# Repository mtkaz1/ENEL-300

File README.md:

## Overview

This project is a **Bluetooth-controlled remote robot** built by a 4-member team to compete in an obstacle course and metal/object detection challenge, where we placed **Top 10**. The robot combines custom PCB design, embedded firmware, and real-time sensor integration to navigate obstacles and detect objects autonomously and via manual override.

## Key Features

- **Bluetooth Control**: Real-time remote driving via a Bluetooth serial link, allowing manual navigation through the obstacle course alongside autonomous detection routines.
- **ESP32 Firmware (C)**: Core embedded logic written in **C**, handling motor control via **PWM**, sensor polling, and Bluetooth command parsing simultaneously.
- **Remote Control App (Python)**: Built a **Python** application to send driving commands over Bluetooth, giving the operator real-time manual control during competition runs.
- **Custom PCB Design**: Designed and fabricated a custom PCB to consolidate power distribution, motor drivers, and sensor connections, reducing wiring complexity and improving reliability during competition runs.
- **Object/Metal Detection**: Integrated sensors for object and metal detection, feeding data back to the ESP32 for navigation decisions.
- **PWM Motor Control**: Used **PWM** signals to precisely control motor speed and direction, enabling fine-tuned maneuvering through tight obstacle course sections.

## Development Process

Our team of 4 applied a sprint-based workflow, using Gantt charts and weekly check-ins to track progress and keep hardware and firmware development in sync. This let us parallelize PCB fabrication, firmware development, and mechanical assembly, then integrate and test the full system ahead of competition.

## Results

The robot placed **Top 10** in the obstacle course and object detection competition, validating both the reliability of our custom PCB/hardware stack and the responsiveness of our Bluetooth control and detection firmware under competition conditions.

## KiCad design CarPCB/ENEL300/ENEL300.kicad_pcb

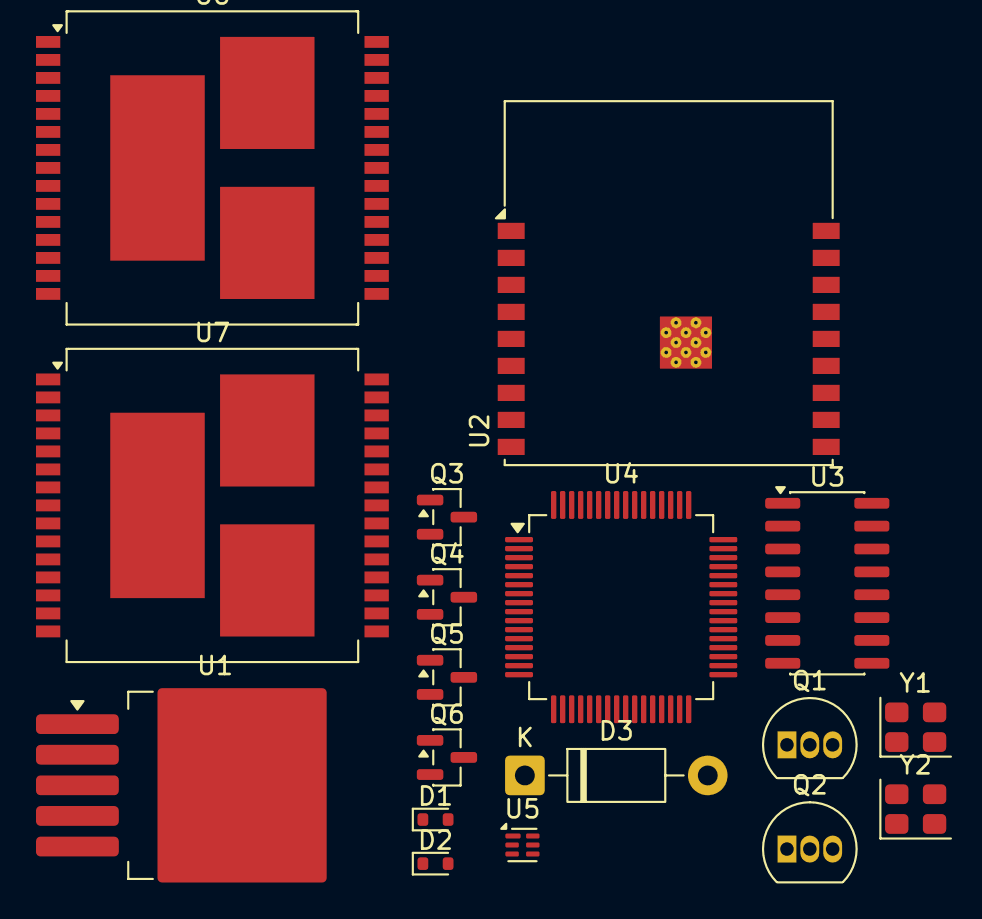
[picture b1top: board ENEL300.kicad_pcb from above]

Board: 2 copper layers, 18 parts (0 on the bottom side), 25 nets, no tracks yet.

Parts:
D1, D2: ESD5Zxx; D_SOD-523
D3: 1N5824; D_DO-41_SOD81_P10.16mm_Horizontal
Q1, Q2: 2N3904; TO-92_Inline
Q3, Q4, Q5, Q6: 2N7002E; SOT-23
U1: LM2596S-5; TO-263-5_TabPin3
U2: ESP32-C3-WROOM-02
U3: CH340C; SOIC-16_3.9x9.9mm_P1.27mm
U4: STM32F446RETx; LQFP-64_10x10mm_P0.5mm
U5: BQ297xy; WSON-6_1.5x1.5mm_P0.5mm
U6, U7: VNH5019A-E; ST_MultiPowerSO-30
Y1, Y2: ASE-xxxMHz; Oscillator_SMD_Abracon_ASE-4Pin_3.2x2.5mm

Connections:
+3.3V: U1.4 (FB), U2.1 (3V3), U3.16 (VCC), U4.1 (VBAT), U4.19 (VDD), U4.32 (VDD), U4.48 (VDD), U4.64 (VDD), Y1.4 (Vdd), Y2.4 (Vdd)
+BATT: Q5.2 (S), Q6.2 (S), U1.1 (VIN), U6.12 (VBAT), U7.12 (VBAT)
GND: D3.2 (A), Q1.1 (E), Q1.3 (C), Q2.1 (E), Q4.2 (S), U1.3 (GND), U1.5 (~ON/OFF), U2.8 (IO9), U2.9 (GND), U2.19 (GND), U3.1 (GND), U4.12 (VSSA), U4.18 (VSS), U4.31 (VSS), U4.47 (VSS), U4.63 (VSS), U6.18 (GNDB), U6.19 (GNDB), U6.20 (GNDB), U6.26 (GNDA), U6.27 (GNDA), U6.28 (GNDA), U7.18 (GNDB), U7.19 (GNDB), U7.20 (GNDB), U7.26 (GNDA), U7.27 (GNDA), U7.28 (GNDA), Y1.2 (GND), Y2.2 (GND)
unnamed: Q3.2 (S), U5.4 (VSS)
unnamed: D3.1 (K), U1.2 (OUT)
unnamed: U6.1 (OUTA), U6.25 (OUTA), U6.30 (OUTA), U6.33 (OUTA)
unnamed: U6.15 (OUTB), U6.16 (OUTB), U6.21 (OUTB), U6.32 (OUTB)
unnamed: U7.1 (OUTA), U7.25 (OUTA), U7.30 (OUTA), U7.33 (OUTA)
unnamed: U7.15 (OUTB), U7.16 (OUTB), U7.21 (OUTB), U7.32 (OUTB)
unnamed: Q2.3 (C), U2.2 (EN)
unnamed: Q3.3 (D), Q4.3 (D)
unnamed: Q3.1 (G), U5.3 (Dout)
unnamed: Q4.1 (G), U5.2 (Cout)
unnamed: Q5.3 (D), U6.3 (VCC), U6.13 (VCC), U6.23 (VCC), U6.31 (VCC)
unnamed: Q5.1 (G), U6.11 (CP)
unnamed: Q6.3 (D), U7.3 (VCC), U7.13 (VCC), U7.23 (VCC), U7.31 (VCC)
unnamed: Q6.1 (G), U7.11 (CP)
unnamed: U2.18 (IO0), Y1.1 (EN)
unnamed: U2.17 (IO1), Y1.3 (OUT)
unnamed: U2.11 (IO20/RXD), U3.2 (TXD)
unnamed: U2.12 (IO21/TXD), U3.3 (RXD)
unnamed: U4.9 (PC1), U4.39 (PC8)
unnamed: U4.5 (PH0), Y2.1 (EN)
unnamed: U4.6 (PH1), Y2.3 (OUT)
unnamed: U5.5 (BAT), U5.6 (V-)

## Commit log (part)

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2026-03-04 Remove large STEP file
2026-03-04 adding stm32 code
2026-03-06 asdfghj
2026-03-06 Create BOM
2026-04-03 Adding the completed firmware for our ESP32
2026-04-25 Uploading the completed Firmware and controller code with PlatformIO
